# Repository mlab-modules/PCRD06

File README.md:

<!--- PrjInfo ---> <!--- Please remove this line after manually editing --->
<!--- 00a56be08b96043df9e37d6aff7b6990 --->
<!--- Created:2019-08-04 12:46:39.528455: --->
<!--- Author:: --->
<!--- AuthorEmail:: --->
<!--- Tags:: --->
<!--- Ust:: --->
<!--- Label --->
<!--- ELabel --->
<!--- Name:PCRD06A: --->
# PCRD06A Sample and hold circuit with analog memory
<!--- LongName --->
Signal follower with analog memory. It is a circuit equivalent to a sample-hold circuit triggered by a falling edge of signal or a circuit equivalent to a peak detector. The PCRD06A module is normally used in combination with SiPM based scintillation detector.

Examples of detectors that could be connected to the PCRD analog-backend.

  * [SIMP02](https://github.com/mlab-modules/SIPM02)
  * [USTSIPM01](https://github.com/ust-modules/USTSIPM01)

<!--- ELongName --->

<!--- Lead --->

<!--- ELead --->

<!--- Description --->

### Basic usage 

The circuit is able to operate in multiple modes. The operation mode depends on the logic used to control the circuit.  

  1. The first operation mode is the peak detector, which stores the maximal value of peak output from SiPM. This mode holds the maximal value of pulse until the circuit is reset (usually after AD conversion)
  2. Pulse discriminator, where the AD converted value is compared with a predefined threshold. After passing this threshold the circuit should be reset. 
  3. The energy integrator in that mode signal is ADconverted as fast as possible, and the dose is integrated numerically over the specified time interval. 

### Principle of function 

The signal output from the scintillation detector is a pulse. The pulses are stored in a specially developed sample-hold circuit that behaves as a signal follower and analog memory. When signal #PeakDetect_Trace is in H an analog switch U5 turns on and a signal at an output U2 follows a signal at the input with a slight delay which is done by R13 and C19. If signal #PeakDetect_Trace is switched to a high impedance state the analog switch U5 starts to be controlled by a comparator U1. In this case, when the input signal goes from high to low, a positive input of the comparator will be at a higher voltage than a negative input, following a voltage at capacitor C19.

It causes the switching-off of the analog switch U5 and the capacitor C19 holds its last voltage value. This behavior is similar to a peak detector circuit. In the next step, the stored voltage can be converted by ADC connected at the output and after this conversion, the input #PeakDetect_Trace goes again to H and the circuit changes behavior to signal follower circuit. The described sample-hold circuit does not suffer from typical peak detector circuit ills like insensitivity to small signals, mistreatment of negative signals, or discharging the capacitor by leakage current through diodes.

Moreover, this circuit can be used as a pulse discriminator as well. The signal #PeakDetect_Trace can be connected to an input of digital circuits when it is controlled by the comparator U1. When the input signal goes from high to low, the signal #PeakDetect_Trace goes from high to low as well. This behavior can be used for the detection of the falling edge of the signal. There is only one constraint of this circuit, the input signal can not change raising/falling time widely and the RC time constant (R13, C19) must be chosen correctly, respecting the input signal time properties.

More details about the principle are in [DOCTORAL THESIS, Research on cosmic rays on board aircraft using a newly developed PIN diode detector, 2020, CTU in Prague](http://www.ujf.cas.cz/export/sites/ujf/.content/files/CRREAT/kakona_thesis.pdf)

<!--- EDescription --->
<!--- Content --->
<!--- EContent --->
<sub><sup> Generated with [MLABweb](https://github.com/MLAB-project/MLABweb). (2019-08-04)</sup></sub>

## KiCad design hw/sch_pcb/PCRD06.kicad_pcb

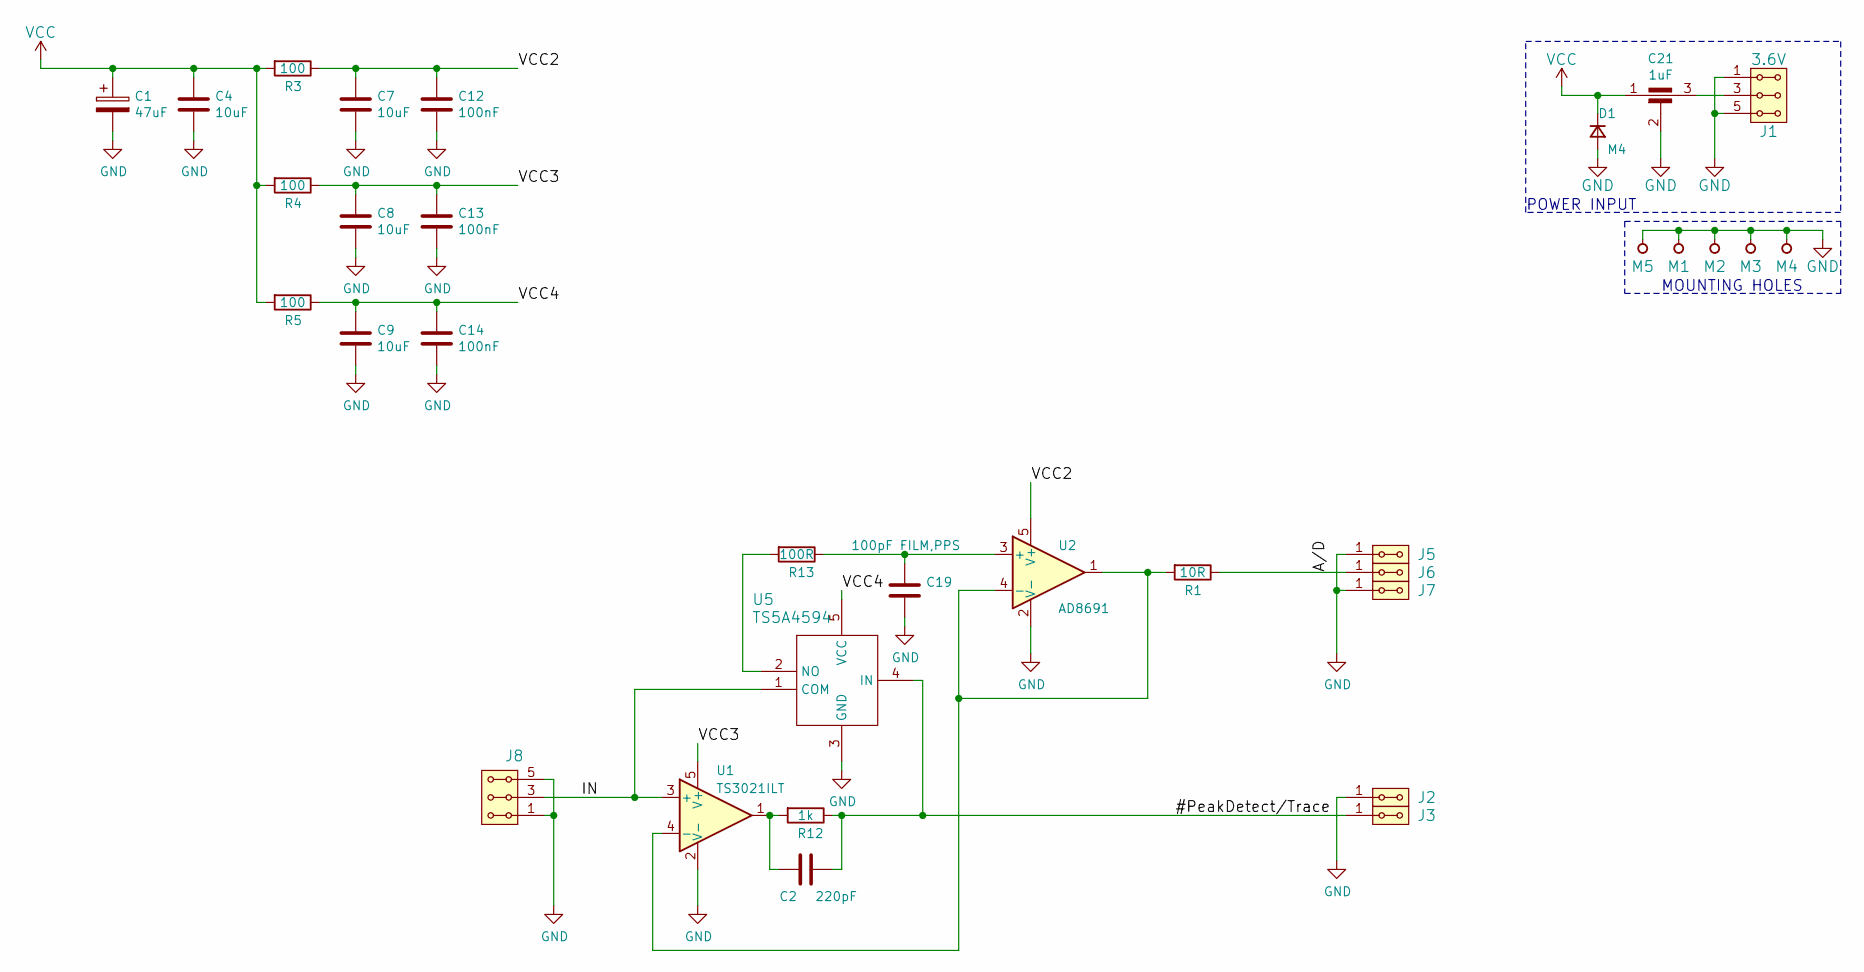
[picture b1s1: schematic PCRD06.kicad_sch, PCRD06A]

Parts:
C1: 47uF; TantalC_SizeC_Reflow
C2: 220pF; SMD-0805
C4, C7, C8, C9: 10uF; SMD-0805
C12, C13, C14: 100nF; SMD-0805
C19: 100pF FILM,PPS; SMD-0805
C21: 1uF; FIR_0805
D1: M4; Diode-SMA_Standard
J1: 3.6V; Straight_2x03
J2, J3, J5, J6, J7: HEADER_2x01_PARALLEL; Straight_2x01
J8: HEADER_2x03_PARALLEL; Straight_2x03
M1, M2, M3, M4: HOLE; MountingHole_3mm
M5: HOLE; Laird_Technologies_BMI-S-204-F_32.00x32.00mm
R1: 10R; SMD-0805
R3, R4, R5: 100; SMD-0805
R12: 1k; SMD-0805
R13: 100R; SMD-0805
U1: TS3021ILT; SOT-23-5_HandSoldering
U2: AD8691; TSOT-23-5_HandSoldering
U5: TS5A4594; SOT-23-5_HandSoldering

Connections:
/#PeakDetect/Trace: C2.1, J3.1, J3.2, R12.1, U5.4 (IN)
/A/D: J6.1, J6.2, R1.1
/IN: J8.3, J8.4, U1.3 (+), U5.1 (COM)
/VCC2: C7.1, C12.1, R3.1, U2.5 (V+)
/VCC3: C8.1, C13.1, R4.1, U1.5 (V+)
/VCC4: C9.1, C14.1, R5.1, U5.5 (VCC)
GND: C1.2, C4.2, C7.2, C8.2, C9.2, C12.2, C13.2, C14.2, C19.2, C21.2, D1.2 (A), J1.1, J1.2, J1.5, J1.6, J2.1, J2.2, J5.1, J5.2, J7.1, J7.2, J8.1, J8.2, J8.5, J8.6, M1.1, M2.1, M3.1, M4.1, M5.1, U1.2 (V-), U2.2 (V-), U5.3 (GND)
unnamed: C2.2, R12.2, U1.1
unnamed: C19.1, R13.1, U2.3 (+)
unnamed: C21.3, J1.3, J1.4
unnamed: R1.2, U1.4 (-), U2.1, U2.4 (-)
unnamed: R13.2, U5.2 (NO)
VCC: C1.1, C4.1, C21.1, D1.1 (K), R3.2, R4.2, R5.2

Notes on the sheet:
MOUNTING HOLES
POWER INPUT

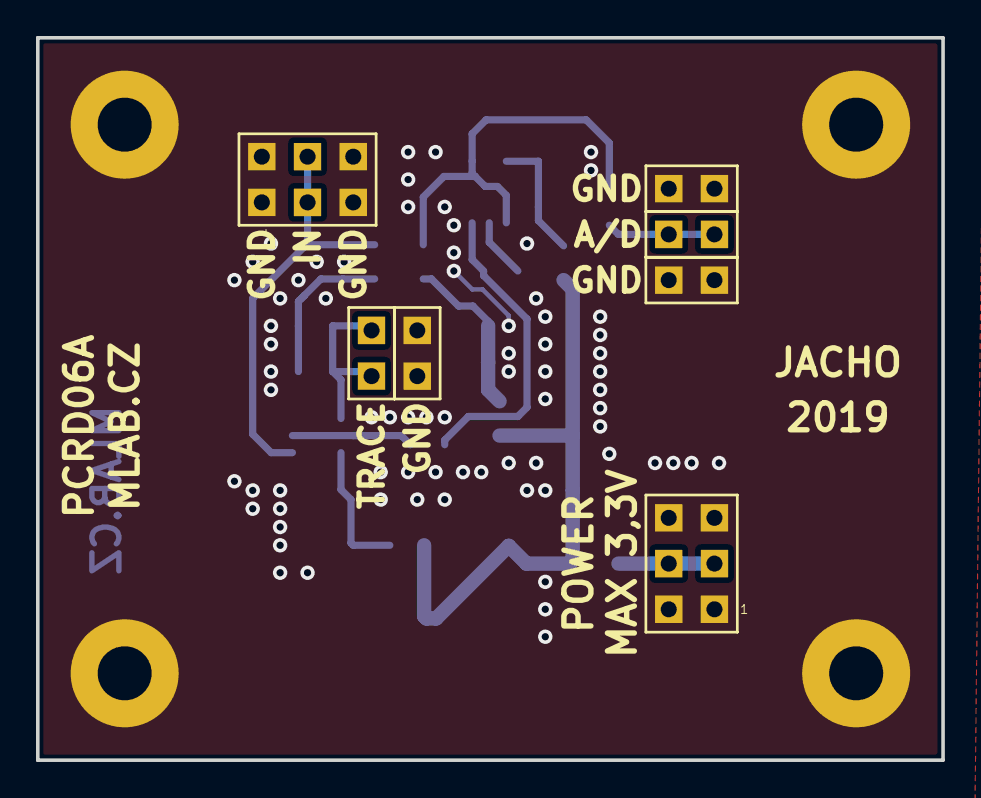
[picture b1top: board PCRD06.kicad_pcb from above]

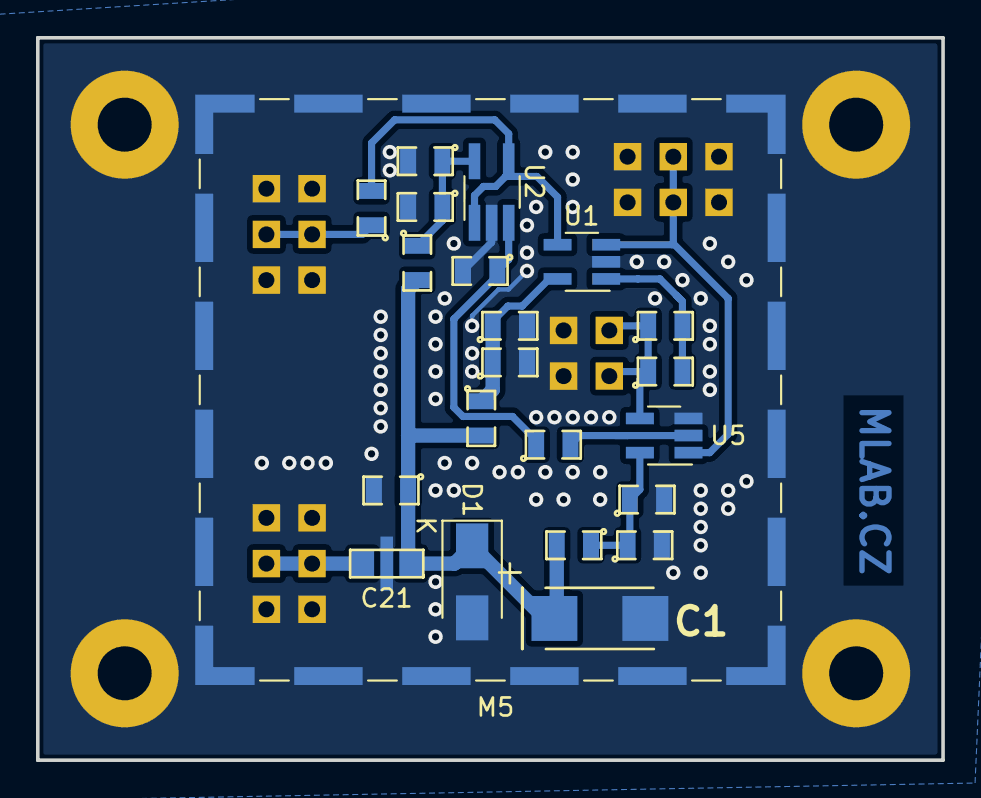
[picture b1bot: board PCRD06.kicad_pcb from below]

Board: 2 copper layers, 50.3 x 40.1 mm, 33 parts (22 on the bottom side), 13 nets.

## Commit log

2019-08-04 [MLABweb] Documentation edits; PCRD06A
2019-08-05 edit
2019-08-05 Edit PCB
2019-08-06 Generovani vyrobnich dat
2019-11-08 Generovana vyrobni data
2020-11-04 Fix license
2021-02-11 Přegenerování výrobních dat.
2021-04-03 Nové reálné fotky
2021-12-31 Update documentation.
2022-01-12 New proposed design of future variant.
2022-04-06 automated commit; add github actions
2022-04-06 Update actions products
2023-02-14 update actions
2023-02-14 Update metadata files
2023-07-05 automated commit; rename source files to new naming convence
2023-09-08 Update README.md
    Improve clarity and spell-check.
2023-09-09 Add links to datasheets.
2023-09-16 Update status
2023-09-17 Delete PCRD06A.json
    Delete file without useful data.

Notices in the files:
hw/sch_pcb/PCRD06.kicad_sch:
GPL 3
